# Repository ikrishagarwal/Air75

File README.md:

# Air 75

A Macro Pad with rotary encoders and OLED display.

## Specifications

### BOM

- 9x Cherry MX Switches
- 9x Blank DSA Keycaps (1x Red, 4x White, 4x Black)
- 1x Rotary Encoder
- 1x 128x32 OLED Display
- 10x 1N4148 Diodes
- 1x XIAO RP2040
- 4x M3x16 Bolt

# Features

- Rotary Encoder Support
- OLED Display Support
- VIA Support
- Based on QMK

### Other Resources

- [PCB](PCB)
- [Images](images)

|              Schematic              |          PCB           |           Case           |
| :---------------------------------: | :--------------------: | :----------------------: |
|  |  |  |

## Author

- [Krish](https://github.com/ikrishagarwal)

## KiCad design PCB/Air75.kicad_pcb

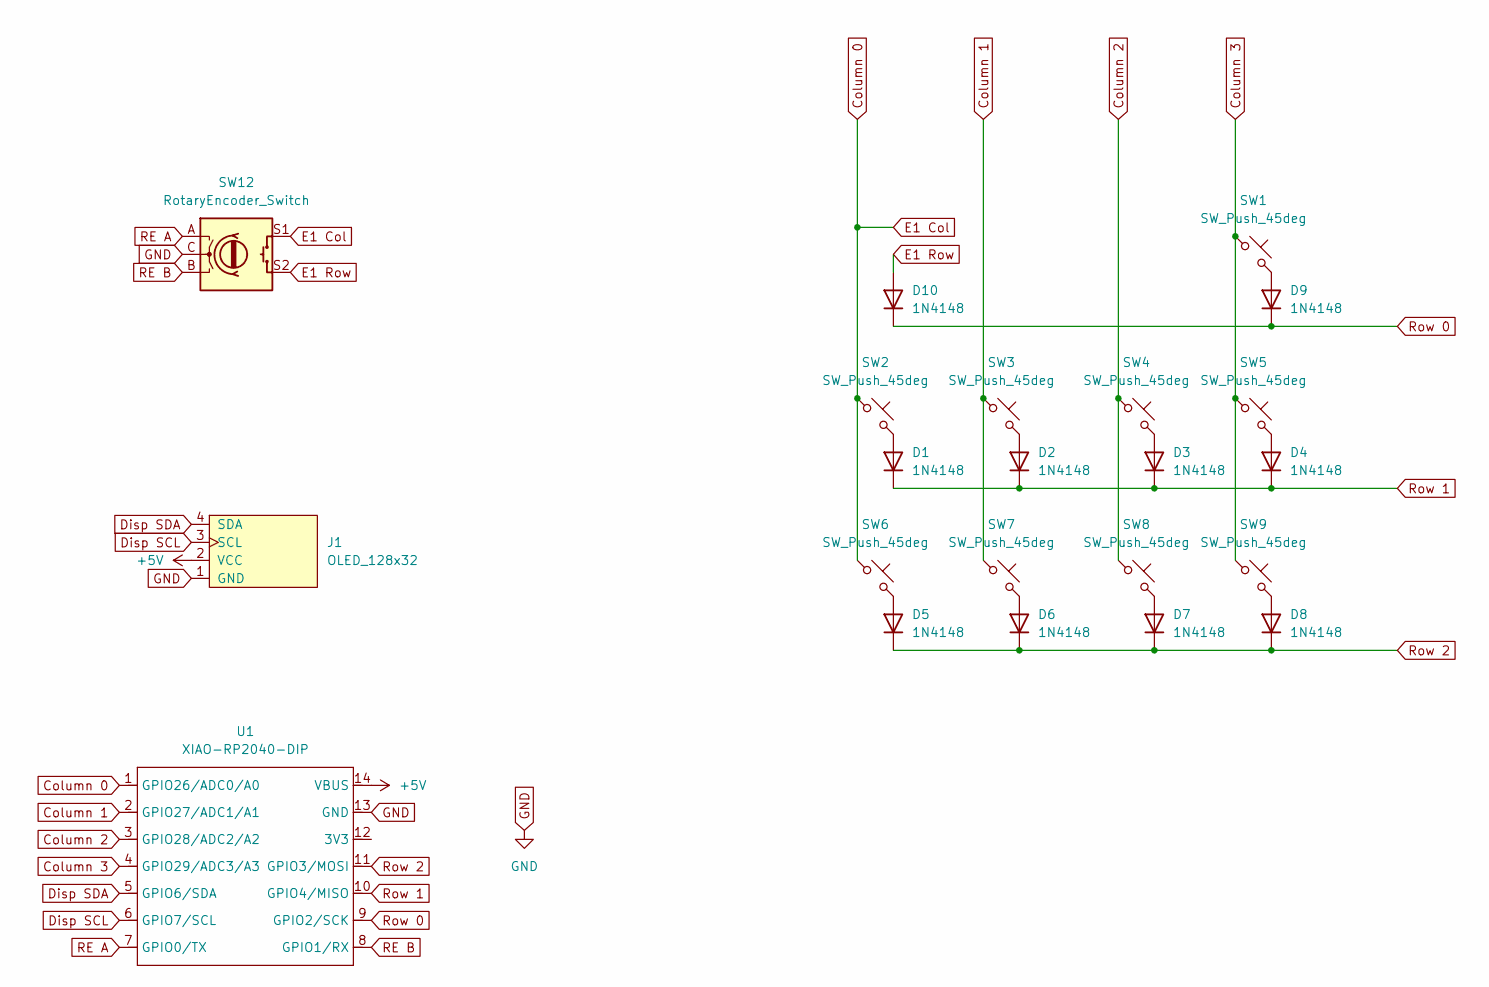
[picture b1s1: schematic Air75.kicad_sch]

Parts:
D1, D2, D3, D4, D5, D6, D7, D8, D9, D10: 1N4148; D_DO-35_SOD27_P7.62mm_Horizontal
J1: OLED_128x32
SW1, SW2, SW3, SW4, SW5, SW6, SW7, SW8, SW9: SW_Push_45deg; SW_Cherry_MX_1.00u_PCB
SW12: RotaryEncoder_Switch; Encoder_EC11_MX_Combo
U1: XIAO-RP2040-DIP

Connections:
+5V: J1.2 (VCC), U1.14 (VBUS)
Column 0: SW2.1, SW6.1, SW12.S1, U1.1 (GPIO26/ADC0/A0)
Column 1: SW3.1, SW7.1, U1.2 (GPIO27/ADC1/A1)
Column 2: SW4.1, SW8.1, U1.3 (GPIO28/ADC2/A2)
Column 3: SW1.1, SW5.1, SW9.1, U1.4 (GPIO29/ADC3/A3)
Disp SCL: J1.3 (SCL), U1.6 (GPIO7/SCL)
Disp SDA: J1.4 (SDA), U1.5 (GPIO6/SDA)
E1 Row: D10.2 (A), SW12.S2
GND: J1.1 (GND), SW12.C, U1.13 (GND)
unnamed: D1.2 (A), SW2.2
unnamed: D2.2 (A), SW3.2
unnamed: D3.2 (A), SW4.2
unnamed: D4.2 (A), SW5.2
unnamed: D5.2 (A), SW6.2
unnamed: D6.2 (A), SW7.2
unnamed: D7.2 (A), SW8.2
unnamed: D8.2 (A), SW9.2
unnamed: D9.2 (A), SW1.2
RE A: SW12.A, U1.7 (GPIO0/TX)
RE B: SW12.B, U1.8 (GPIO1/RX)
Row 0: D9.1 (K), D10.1 (K), U1.9 (GPIO2/SCK)
Row 1: D1.1 (K), D2.1 (K), D3.1 (K), D4.1 (K), U1.10 (GPIO4/MISO)
Row 2: D5.1 (K), D6.1 (K), D7.1 (K), D8.1 (K), U1.11 (GPIO3/MOSI)

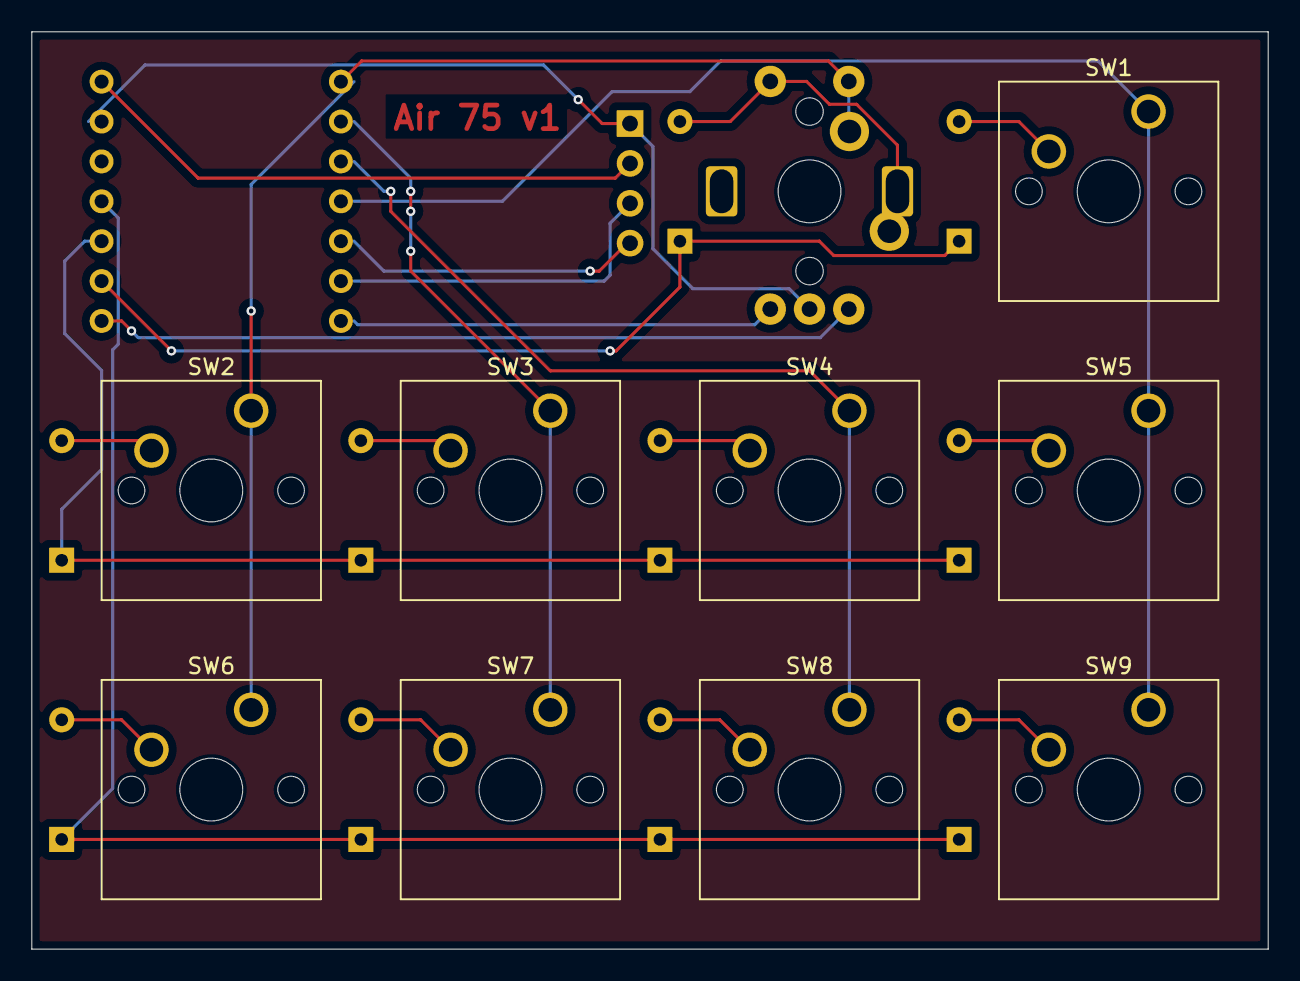
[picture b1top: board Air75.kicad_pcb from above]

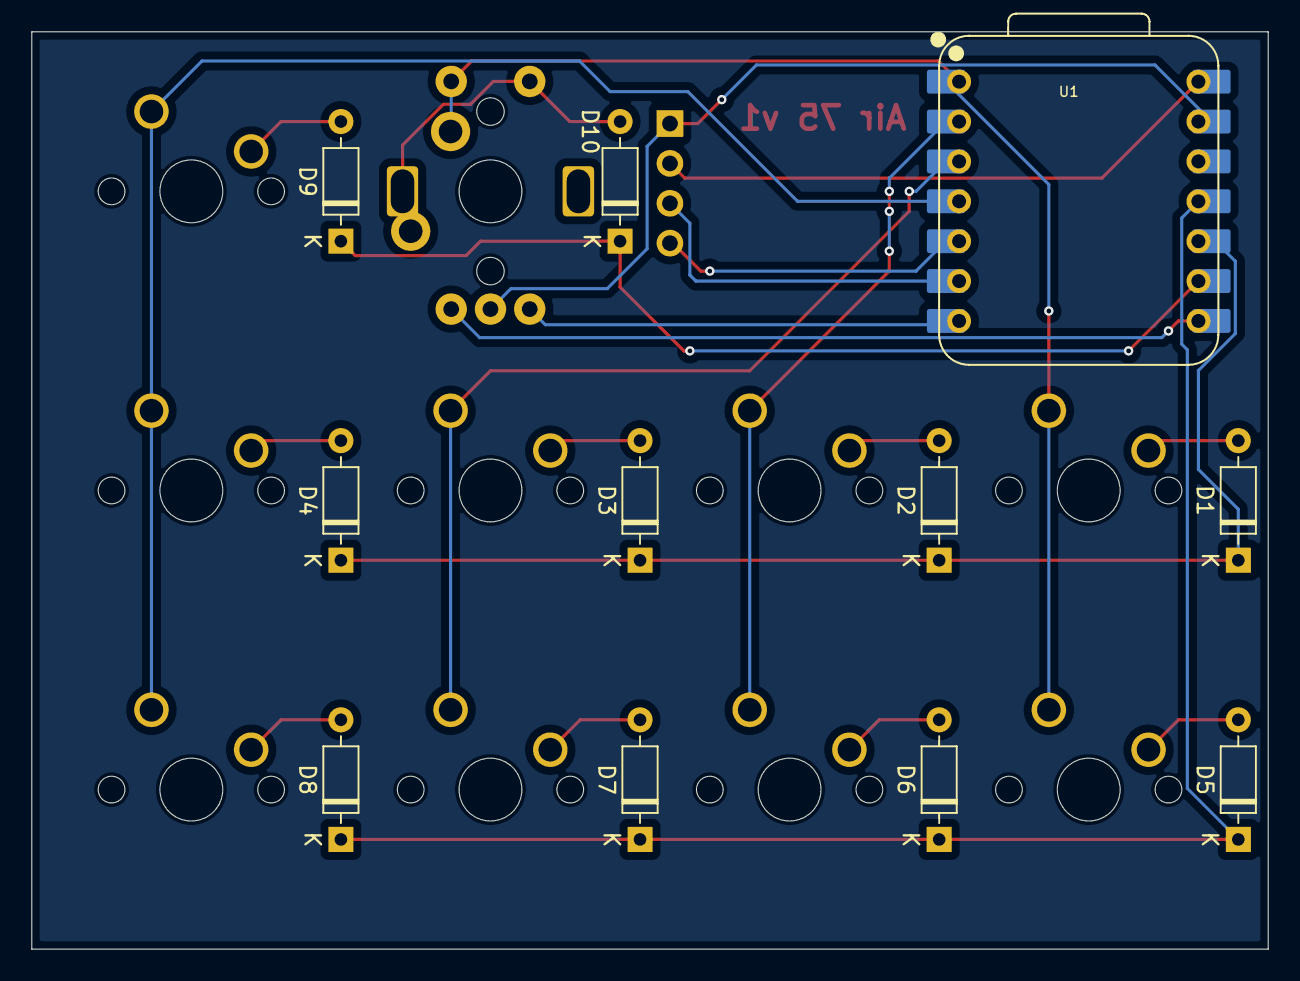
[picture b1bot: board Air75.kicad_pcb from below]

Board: 2 copper layers, 78.7 x 58.4 mm, 22 parts (11 on the bottom side), 23 nets.

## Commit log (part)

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2025-02-17 made the pcb
2025-02-18 fix: remove right angles from pcb
2025-02-18 fix: fix pcb
2025-02-19 added everything
2026-01-03 feat: mess commit for old firmware
2026-01-03 feat: switch to qmk
2026-01-04 feat: customized the OLED
2026-01-04 docs: added images
2026-01-12 fix: keymaps
